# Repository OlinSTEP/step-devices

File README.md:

# Welcome to the STEP Hardware Repository

We plan to focus on designing a wearable that helps people communicate with “smart” technology in an unobtrusive, private, and efficient manner. We want our system to support more natural interactions with smart technologies.

In this repository you'll find all of the hardware projects we've been working on.

### Special thanks to...
* The STEP teaching team (Dr. Alessandra Ferzoco, Dr. Caitrin Lynch, Dr. Sam Michalka, Dr. Paul Ruvolo) for doing a phenomenal job desiging and leading the class
* Olin College of Engineering for providing us with space and resources
* [Olin Electric Motorsports](https://www.olinelectricmotorsports.com/) for inspiring a lot of our repository infrastructure, documentation, and workflow (check out their respoitory by [clicking here](https://github.com/olin-electric-motorsports/olin-electric-motorsports))

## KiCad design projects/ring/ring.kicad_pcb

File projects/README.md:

# Work in Progress Projects

## ESP32BLEKeyboardDemo

This uses an Adafruit Feather ESP32 board to present as a Bluetooth keyboard.  The current demo implements four functions when connected to an iPhone with VoiceOver turned on: move VoiceOver cursor to next item, move VoiceOver cursor to previous item, select current item, toggle display of onscreen keyboard.

The heavy lifting on the BLE side is handled by T-vK's [ESP32-BLE-Keyboard library](https://github.com/T-vK/ESP32-BLE-Keyboard).  We did make a minor change to add the media eject button as an additional control.

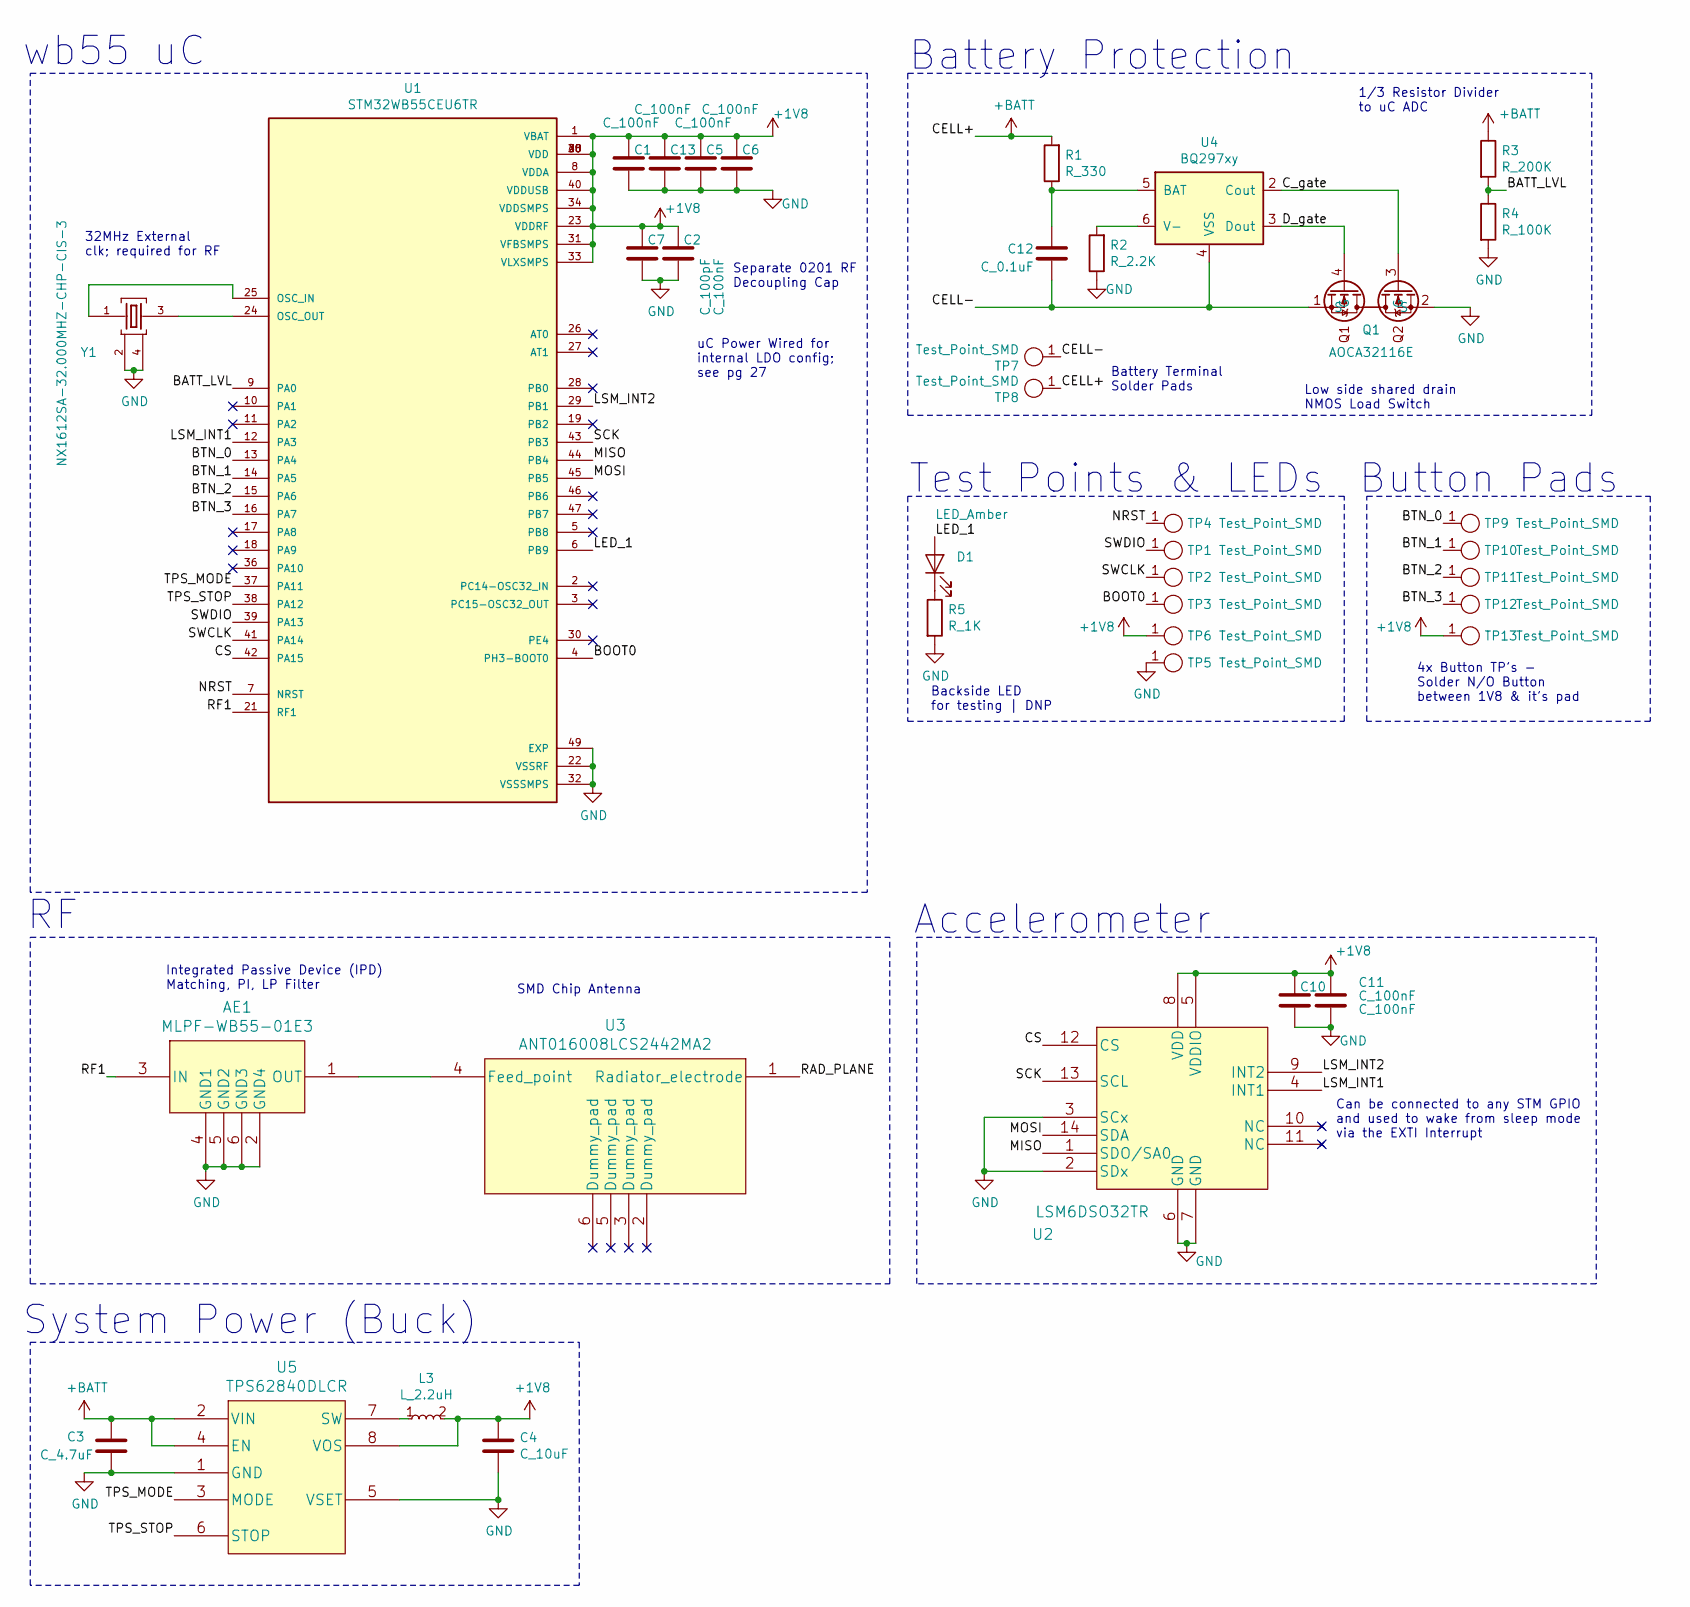
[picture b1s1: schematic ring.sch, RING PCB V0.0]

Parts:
AE1: MLPF-WB55-01E3
C1, C5, C6, C10, C11, C13: C_100nF; C_0402_1005Metric; MPN C0402C104K9RACTU
C2: C_100nF; C_0201_0603Metric; MPN C0402C104K9RACTU
C3: C_4.7uF; C_0402_1005Metric; MPN CL21A475KAQNNNE
C4: C_10uF; C_0402_1005Metric; MPN 1276-1052-1-ND
C7: C_100pF; C_0201_0603Metric; MPN 732-7852-1-ND
C12: C_0.1uF; C_0402_1005Metric; MPN 478-3352-1-ND
D1: LED_Amber; LED_0402_1005Metric; MPN L71517CT-ND
L3: L_2.2uH; L_0805_2012Metric_Pad1.05x1.20mm_HandSolder; MPN DFE201612E-2R2M=P2
Q1: AOCA32116E
R1: R_330; R_0402_1005Metric; MPN RMCF0805FT330RCT-ND
R2: R_2.2K; R_0402_1005Metric; MPN RMCF0805FT2K20CT-ND
R3: R_200K; R_0402_1005Metric; MPN P300KDACT-ND
R4: R_100K; R_0402_1005Metric; MPN P100KCCT-ND
R5: R_1K; R_0402_1005Metric; MPN RNCP0805FTD1K00CT-ND
TP1, TP2, TP3, TP4, TP5, TP6, TP9, TP10, TP11, TP12, TP13: Test_Point_SMD; TestPoint_Pad_1.0x1.0mm
TP7, TP8: Test_Point_SMD; TestPoint_Pad_1.5x1.5mm
U1: STM32WB55CEU6TR; QFN50P700X700X60-49N; PARTREV 5
U2: LSM6DSO32TR
U3: ANT016008LCS2442MA2
U4: BQ297xy; WSON-6_1.5x1.5mm_P0.5mm
U5: TPS62840DLCR
Y1: NX1612SA-32.000MHZ-CHP-CIS-3; OSCSC105P160X120X35-4N

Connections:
+1V8: C1.1, C2.1, C4.1, C5.1, C6.1, C7.1, C10.1, C11.1, C13.1, L3.2, TP6.1, TP13.1, U1.1 (VBAT), U1.8 (VDDA), U1.20 (VDD), U1.23 (VDDRF), U1.31 (VFBSMPS), U1.33 (VLXSMPS), U1.34 (VDDSMPS), U1.35 (VDD), U1.40 (VDDUSB), U1.48 (VDD), U2.5 (VDDIO), U2.8 (VDD), U5.8 (VOS)
+BATT: C3.1, R1.2, R3.1, TP8.1, U5.2 (VIN), U5.4 (EN)
/BATT_LVL: R3.2, R4.1, U1.9 (PA0)
/BOOT0: TP3.1, U1.4 (PH3-BOOT0)
/BTN_0: TP9.1, U1.13 (PA4)
/BTN_1: TP10.1, U1.14 (PA5)
/BTN_2: TP11.1, U1.15 (PA6)
/BTN_3: TP12.1, U1.16 (PA7)
/CELL-: C12.2, Q1.1 (S), TP7.1, U4.4 (VSS)
/CS: U1.42 (PA15), U2.12 (CS)
/C_gate: Q1.3 (G), U4.2 (Cout)
/D_gate: Q1.4 (G), U4.3 (Dout)
/LED_1: D1.2 (A), U1.6 (PB9)
/LSM_INT1: U1.12 (PA3), U2.4 (INT1)
/LSM_INT2: U1.29 (PB1), U2.9 (INT2)
/MISO: U1.44 (PB4), U2.1 (SDO/SA0)
/MOSI: U1.45 (PB5), U2.14 (SDA)
/NRST: TP4.1, U1.7 (NRST)
/RAD_PLANE: U3.1 (Radiator_electrode)
/RF1: AE1.3 (IN), U1.21 (RF1)
/SCK: U1.43 (PB3), U2.13 (SCL)
/SWCLK: TP2.1, U1.41 (PA14)
/SWDIO: TP1.1, U1.39 (PA13)
/TPS_MODE: U1.37 (PA11), U5.3 (MODE)
/TPS_STOP: U1.38 (PA12), U5.6 (STOP)
GND: AE1.2 (GND4), AE1.4 (GND1), AE1.5 (GND2), AE1.6 (GND3), C1.2, C2.2, C3.2, C4.2, C5.2, C6.2, C7.2, C10.2, C11.2, C13.2, Q1.2 (S), R2.1, R4.2, R5.2, TP5.1, U1.22 (VSSRF), U1.32 (VSSSMPS), U1.49 (EXP), U2.2 (SDx), U2.3 (SCx), U2.6 (GND), U2.7 (GND), U5.1 (GND), U5.5 (VSET), Y1.2, Y1.4
unnamed: AE1.1 (OUT), U3.4 (Feed_point)
unnamed: C12.1, R1.1, U4.5 (BAT)
unnamed: D1.1 (K), R5.1
unnamed: L3.1, U5.7 (SW)
unnamed: R2.2, U4.6 (V-)
unnamed: U1.24 (OSC_OUT), Y1.3
unnamed: U1.25 (OSC_IN), Y1.1

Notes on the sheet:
Can be connected to any STM GPIO and used to wake from sleep mode via the EXTI Interrupt
Accelerometer
Integrated Passive Device (IPD) Matching, PI, LP Filter
SMD Chip Antenna
System Power (Buck)
Test Points & LEDs
Battery Protection
wb55 uC
32MHz External clk; required for RF
Low side shared drain NMOS Load Switch
1/3 Resistor Divider to uC ADC
Battery Terminal Solder Pads
Backside LED for testing | DNP
Button Pads
4x Button TP's - Solder N/O Button between 1V8 & it's pad
uC Power Wired for internal LDO config; see pg 27
Separate 0201 RF Decoupling Cap

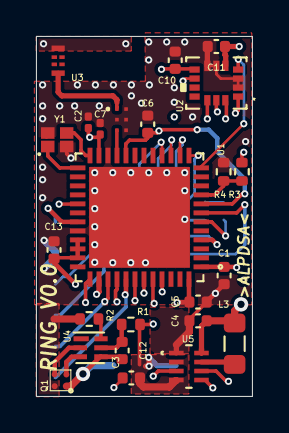
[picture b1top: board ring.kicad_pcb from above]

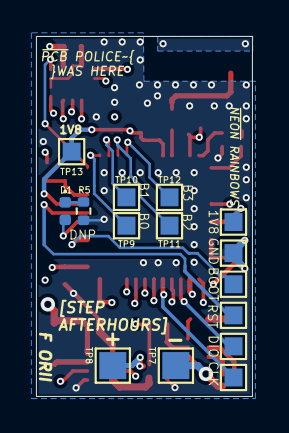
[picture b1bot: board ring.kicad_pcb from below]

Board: 4 copper layers, 12.0 x 20.0 mm, 39 parts (15 on the bottom side), 32 nets.

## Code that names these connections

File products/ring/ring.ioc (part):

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Mcu.Name=STM32WB55CEUx
Mcu.Package=UFQFPN48
Mcu.UserName=STM32WB55CEUx
PA0.Signal=GPIO_Analog
PA11.Signal=GPIO_Output
PA12.Signal=GPIO_Output
PA13.Mode=Serial_Wire
PA13.Signal=SYS_JTMS-SWDIO
PA14.Mode=Serial_Wire
PA14.Signal=SYS_JTCK-SWCLK
PA15.Signal=SPI1_NSS
PA3.Signal=GPXTI3
PA4.Signal=GPXTI4
PA5.Signal=GPXTI5
PA6.Signal=GPXTI6
PA7.Signal=GPXTI7
PB1.Signal=GPXTI1
PB3.Mode=Full_Duplex_Master
PB3.Signal=SPI1_SCK
PB4.Mode=Full_Duplex_Master
PB4.Signal=SPI1_MISO
PB5.Mode=Full_Duplex_Master
PB5.Signal=SPI1_MOSI
PB9.Signal=GPIO_Output
RCC.HSE_VALUE=32000000
RCC.SYSCLKFreq_VALUE=32000000
board=custom

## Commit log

2022-03-03 Initial folder structure creation
2022-03-03 new library created
2022-03-04 Rename symbols library
2022-03-04 Add gitignore with KiCad template
2022-03-04 Set theme jekyll-theme-slate
2022-03-04 Initial commit for github pages
2022-03-04 Add brief repo description to docs
2022-03-04 Initial outline for adding/modifying components doc
2022-03-04 Separate step headers and paragraphs
2022-03-04 List symbol properties
2022-03-06 Expand the `Some Special Considerations` section
    This includes the following subsections:
    * If a similar part exists already, use it
    * Making symbol properties visible/invisible
    * Adding keywords
    * Making new pins
2022-03-06 Give thanks to OEM and teaching team
2022-03-06 Change adjectives
2022-03-06 Set theme jekyll-theme-minimal
2022-03-06 Add title and description
2022-03-06 Add subnav plugin
2022-03-06 Remove title auto generation
2022-03-06 Remove plugins
2022-03-06 Add default title back
2022-03-06 Update description
2022-03-06 Add front matter
2022-03-06 Add navigation to default layout
2022-03-06 Implement recursive nagivation menu generation
2022-03-06 Fix url
2022-03-06 Fix link to kicad page
2022-03-06 Implement recursive navigation for current page only
2022-03-06 Update page navigation front matter
2022-03-06 Change formatting
2022-03-06 Fix urls
2022-03-06 Fix front matter formatting
2022-03-06 Test page names
2022-03-07 Debug page titles
2022-03-07 Reset post bug-testing
2022-03-07 Remove nav options for bug testing
2022-03-07 Move paragraph symbols to new location
2022-03-07 Reformat navigation menu
2022-03-07 Remove navigation option
2022-03-07 Add instructions to setup kicad libraries
2022-03-07 Add link to KiCad documentation
2022-03-07 Add components to library
2022-03-30 Fix Digi-Key spelling
2022-03-30 Change part name and add LDO part
2022-03-30 Migrate docs to github wiki
2022-03-30 Add link to wiki
2022-03-30 Change Link to Buy in part library
2022-04-05 Create new brach to figure out toolchain
2022-04-05 Got blinky to work with manual compilation
2022-04-05 updates parts dir based on OEM parts dirs
2022-04-06 Experiment with external dependencies using FetchContent
2022-04-07 ring PCB RF work in progress
2022-04-07 Manual compilation working, CMake still in progress with FetchData
2022-04-07 CMake testing for luke
2022-04-07 Test ExternalProject functionality
2022-04-07 Reorganize cmake structure
2022-04-07 Remove computer specific files
2022-04-07 Change ExternalProject to FetchContent
2022-04-07 CMake should work w/one dep
2022-04-07 CMake isn't where it wasn't, so we need to calculate the error, or, where CMake is subtracted from where CMake wasn't
2022-04-08 Define target libraries
2022-04-08 Write cmake file for compiling project
2022-04-08 Reconfigure compiler flags
2022-04-08 Remove unused files
2022-04-08 Specify MCU in top project directory
2022-04-08 Use variable definition of MCU
2022-04-08 layout and schem changes
2022-04-11 Create README and add thank yous
2022-04-11 Remove reference to website
2022-04-12 Build .bin files alongside .elfs
2022-04-12 Auto populate project file name CMake
2022-04-13 ring hardware schem & layout updates
2022-04-14 nearly complete first pass schem, RF ready for review
2022-04-14 an inch closer to hardware first rev completion
2022-04-14 AOCA NMOS package update
2022-04-14 int2, silkscreen, DRC DRC DRC FUCK
2022-04-15 ready for first review
2022-04-15 ready for first pass fr this time fixed 'spelling':
2022-04-15 Allow for dynamically linked libraries
2022-04-15 Include stm32wb files only if stm32wb specified as micro
2022-04-15 Include stm32cubewb package
2022-04-15 Download linker script separately from libraries
2022-04-15 Pull all libraries from STM32CubeWB
2022-04-16 just shipped first rev :fingers_crossed:
2022-04-19 List all hal files in separate cmake file
2022-04-19 Relocate source and include file lists
2022-04-19 Rename object dependencies
2022-04-21 Remove flags that print unused information
2022-04-21 Write function to setup stm32cubewb per project
2022-04-21 Make configs specific to each project
2022-04-21 Add bt-demo
2022-04-25 Source system_stm32wbxx.c from stm32cubewb dependency
2022-04-25 fixed luke's mistake
2022-04-25 Adjust stm32cubewb setup function to include rtos files
2022-04-25 Inital demo
2022-04-25 Move config files to separate folder
2022-04-25 Remove unused folder
2022-04-25 Standardize CMakeLists.txt
2022-04-25 Remove unused headers
2022-04-25 Fix spelling
2022-05-02 Setup software debounce and internal pullup
2022-05-06 Use CubeMX to generate outline code
2022-05-20 deterioration modeling, schem datasheet adds
2023-03-08 added ESP32 keyboard stuff
2023-03-23 Added multibutton support
2023-03-28 esp32 firmware for button and joystick controllers
2023-05-04 first rev final controller firmware

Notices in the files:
parts and their libraries:
Copyright 2021 Accelerated Designs. All rights reserved.
